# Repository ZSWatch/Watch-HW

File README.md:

# ZSWatch-Watch

## 📑 Table of Contents

- [ZSWatch-Watch](#zswatch-watch)
  - [📑 Table of Contents](#-table-of-contents)
  - [📖 About](#-about)
  - [📂 Directory Breakdown](#-directory-breakdown)
  - [Purchasing](#purchasing)
  - [KiCad library](#kicad-library)
  - [Ressources](#ressources)
  - [👨‍💻 Maintainer](#-maintainer)

## 📖 About

The **ZSWatch-Watch** project provides the hardware design and production files for a smartwatch development board tailored to the ZSWatch ecosystem.
It is built with **KiCad** and integrates a full **CI/CD pipeline** using **KiBot**, ensuring reproducible outputs for documentation, manufacturing, and releases.

Key features:

- 🛠️ Open-source hardware design
- 📦 Automated generation of Gerber, BoM, and documentation via KiBot
- 🔄 Workflow stages (DRAFT → PRELIMINARY → CHECKED → RELEASED) for structured releases
- 📝 Clear documentation and changelog to track progress
- 🌍 Designed with collaboration and transparency in mind

Please check the [wiki](https://github.com/ZSWatch/ZSWatch/wiki) for more information about the project.

You can also view this project on [CADLAB.io](...).

## 📂 Directory Breakdown

- **`.github`**: GitHub related files
- **`.gitignore`**: Ignored files list
- **`docs`**: Drawings and documentation
- **`kicad-library`**: Pinned KiCad library (submodule)
- **`scripts`**: Additional scripts for CI/CD
- **`watch`**: KiCad project for the watch
- **`CHANGELOG.md`**: Version history
- **`LICENSE`**: Project license (GPL-3.0)
- **`README.md`**: Project overview

The manufacturing outputs (Gerbers, BoM, documentation, etc.) are not part of the repository. They are
attached to each [release](https://github.com/ZSWatch/Watch-HW/releases) and published on GitHub Pages.

## Purchasing

TBD

## KiCad library

Initialize the pinned library after cloning:

```sh
git submodule update --init -- kicad-library
```

## Ressources

- [KiBot Template](https://github.com/nguyen-v/KDT_Hierarchical_KiBot)

## 👨‍💻 Maintainer

- [Daniel Kampert](mailto:danielkameprt@kampis-elektroecke.de)

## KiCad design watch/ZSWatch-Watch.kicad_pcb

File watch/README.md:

<h1 align="center">ZSWatch-Watch</h1>

<p align="center" width="100%">
  
</p>

***

<p align="center">
  
&nbsp; &nbsp; &nbsp; &nbsp;
  
</p>

***

## SPECIFICATIONS

| Parameter | Value |
| --- | --- |
| Dimensions | 32.0 × 24.0 mm |

***

## PROJECT DIRECTORY STRUCTURE

    .
    ├─ kibot_resources       # External resources for KiBot
    │  ├─ colors             # Color theme for KiCad
    │  ├─ fonts              # Fonts used in the project
    │  ├─ scripts            # External scripts used with KiBot
    │  └─ templates          # Templates for KiBot generated reports
    ├─ kibot_yaml            # KiBot YAML config files
    ├─ Logos                 # Logos
    ├─ meta                  # Project metadata
    ├─ templates             # Title block templates
    ├─ *.kicad_sch           # KiCad schematic files
    ├─ *.kicad_pcb           # KiCad PCB layout
    ├─ *.kicad_pro           # KiCad project file
    ├─ *.xml                 # Netlist of the schematic (updated by the pipeline)
    ├─ CHANGELOG.md          # Changelog of the hardware
    ├─ LICENSE               # Project license
    ├─ README.md             # Project README
    └─ kibot_launch.sh       # KiBot automation script

## OUTPUT DIRECTORY STRUCTURE

    .
    ├─ 3D                   # 3D export of the PCB (STEP)
    ├─ HTML                 # HTML files for generated webpage
    ├─ Images               # Pictures and renders
    │  └─ Logos             # Logos
    ├─ KiRI                 # KiRI (PCB diff viewer) files
    ├─ Manufacturing        # Assembly and fabrication documents
    │  ├─ Assembly          # Assembly documents (BoM, BoM check, Mouser cart, pos, notes)
    │  └─ Fabrication       # Fabrication documents (Gerber / ODB++ ZIP, notes, impedance table)
    │     ├─ Drill Tables   # CSV drill tables
    │     └─ Gerbers        # Gerbers
    ├─ Netlist              # PCB netlist
    ├─ Reports              # Reports for ERC/DRC
    ├─ Schematic            # PDF of schematic
    ├─ Testing              # Test documents
    │  └─ Testpoints        # Testpoints tables
    ├─ Variants             # Outputs for assembly variants, if available
    ├─ index.html           # Start page of the generated webpage
    └─ README.md            # This README

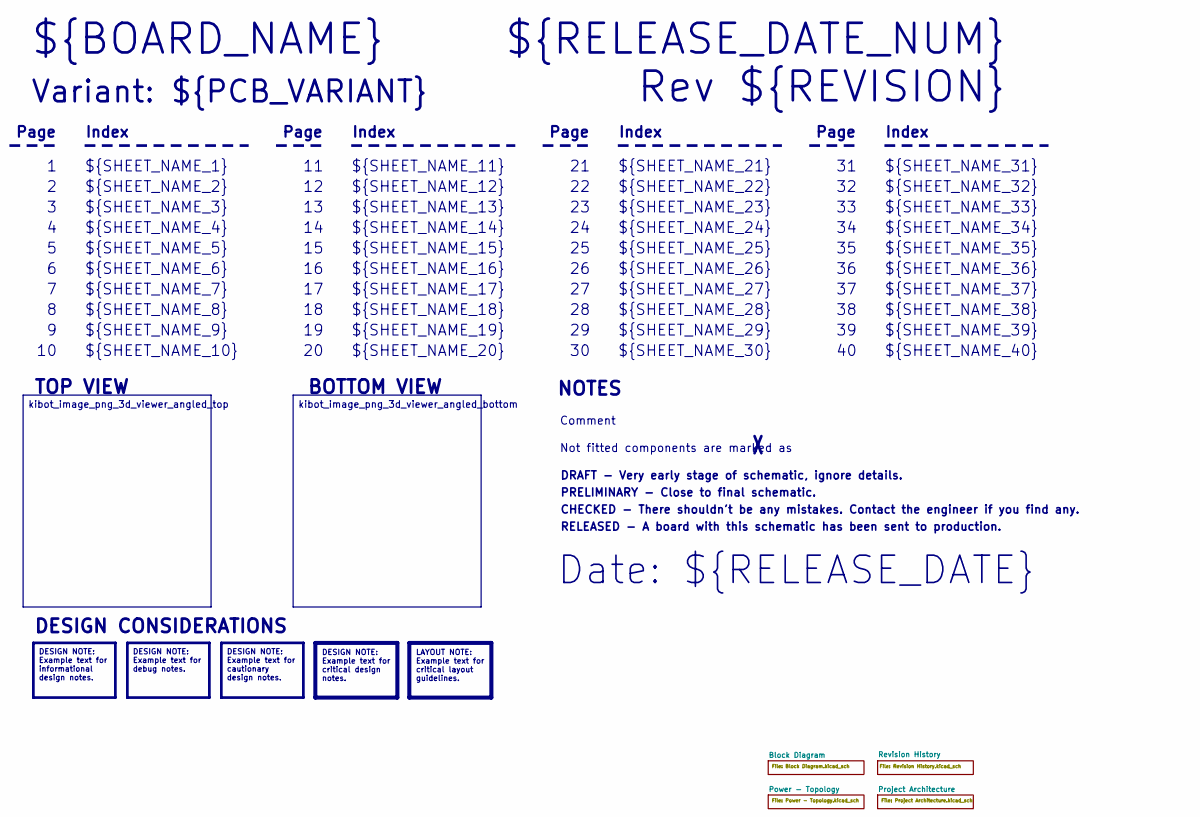
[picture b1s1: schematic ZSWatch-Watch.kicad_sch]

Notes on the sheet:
Variant: ${PCB_VARIANT}
RELEASED - A board with this schematic has been sent to production.
${SHEET_NAME_24}
Index
Page
PRELIMINARY - Close to final schematic.
${SHEET_NAME_22}
DRAFT - Very early stage of schematic, ignore details.
${SHEET_NAME_12}
${SHEET_NAME_8}
${SHEET_NAME_2}
${SHEET_NAME_5}
${SHEET_NAME_20}
${SHEET_NAME_23}
${RELEASE_DATE_NUM}
${SHEET_NAME_35}
Not fitted components are marked as
${SHEET_NAME_11}
${SHEET_NAME_6}
${SHEET_NAME_37}
${SHEET_NAME_26}
${SHEET_NAME_36}
Rev ${REVISION}
${SHEET_NAME_15}
CHECKED - There shouldn't be any mistakes. Contact the engineer if you find any.
BOTTOM VIEW
${SHEET_NAME_14}
${SHEET_NAME_21}
${SHEET_NAME_17}
${SHEET_NAME_18}
Date: ${RELEASE_DATE}
${SHEET_NAME_7}
${SHEET_NAME_31}
${BOARD_NAME}
NOTES
${SHEET_NAME_40}
${SHEET_NAME_39}
${SHEET_NAME_32}
${SHEET_NAME_1}
${SHEET_NAME_9}

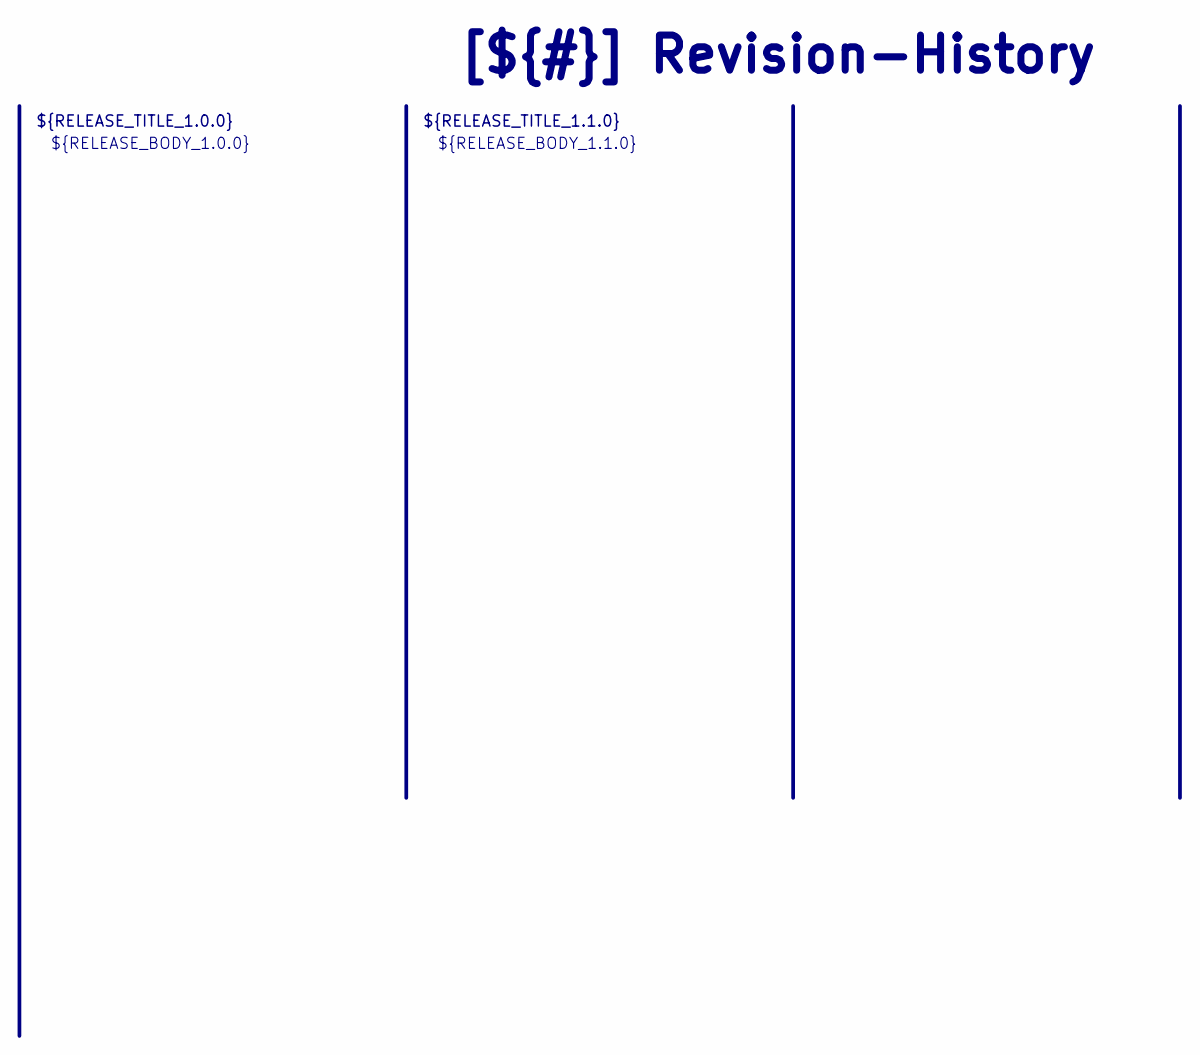
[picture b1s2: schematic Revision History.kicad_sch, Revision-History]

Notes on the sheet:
[${#}] ${TITLE}
${RELEASE_BODY_1.0.0}
${RELEASE_BODY_1.1.0}
${RELEASE_TITLE_1.0.0}
${RELEASE_TITLE_1.1.0}

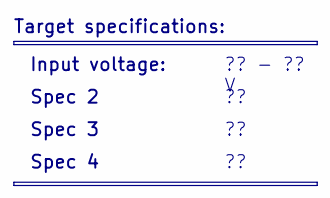
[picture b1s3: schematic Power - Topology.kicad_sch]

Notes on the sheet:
Spec 2
Input voltage:
Spec 4
?? - ?? V
Target specifications:
Spec 3

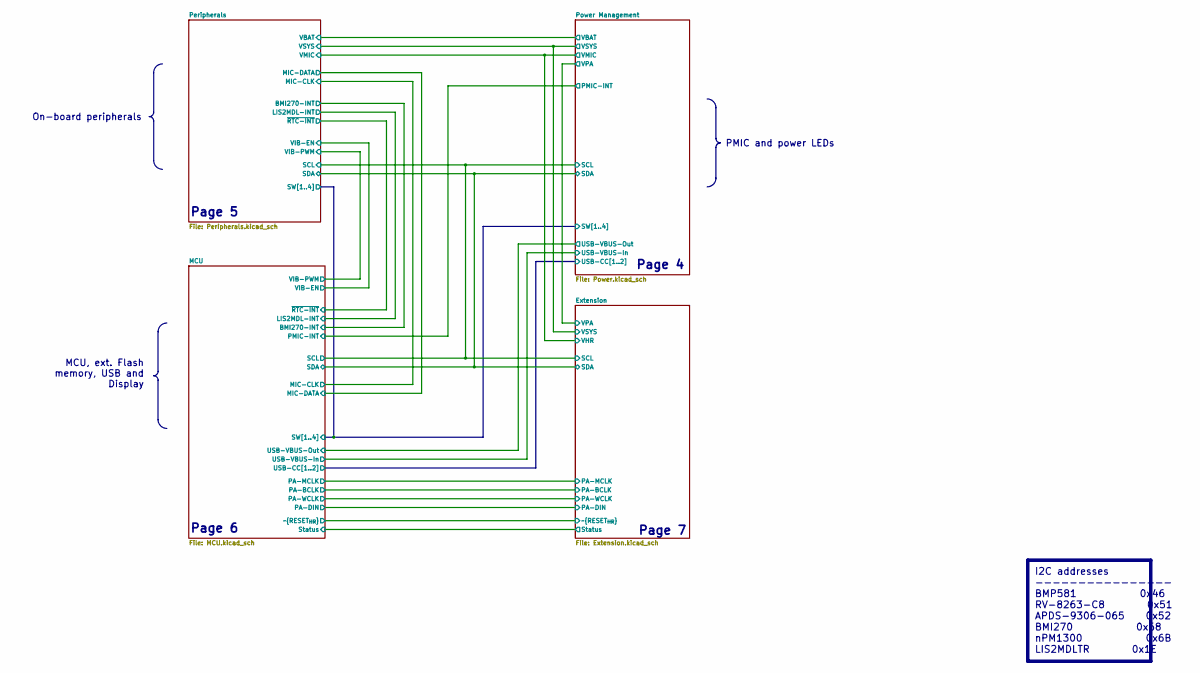
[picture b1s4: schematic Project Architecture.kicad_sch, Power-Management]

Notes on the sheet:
Page 6
Page 4
Page 7
Page 5
MCU, ext. Flash memory, USB and Display
I2C addresses ---------------- BMP581 0x46 RV-8263-C8 0x51 APDS-9306-065 0x52 BMI270 0x68 nPM1300 0x6B LIS2MDLTR 0x1E
On-board peripherals
PMIC and power LEDs

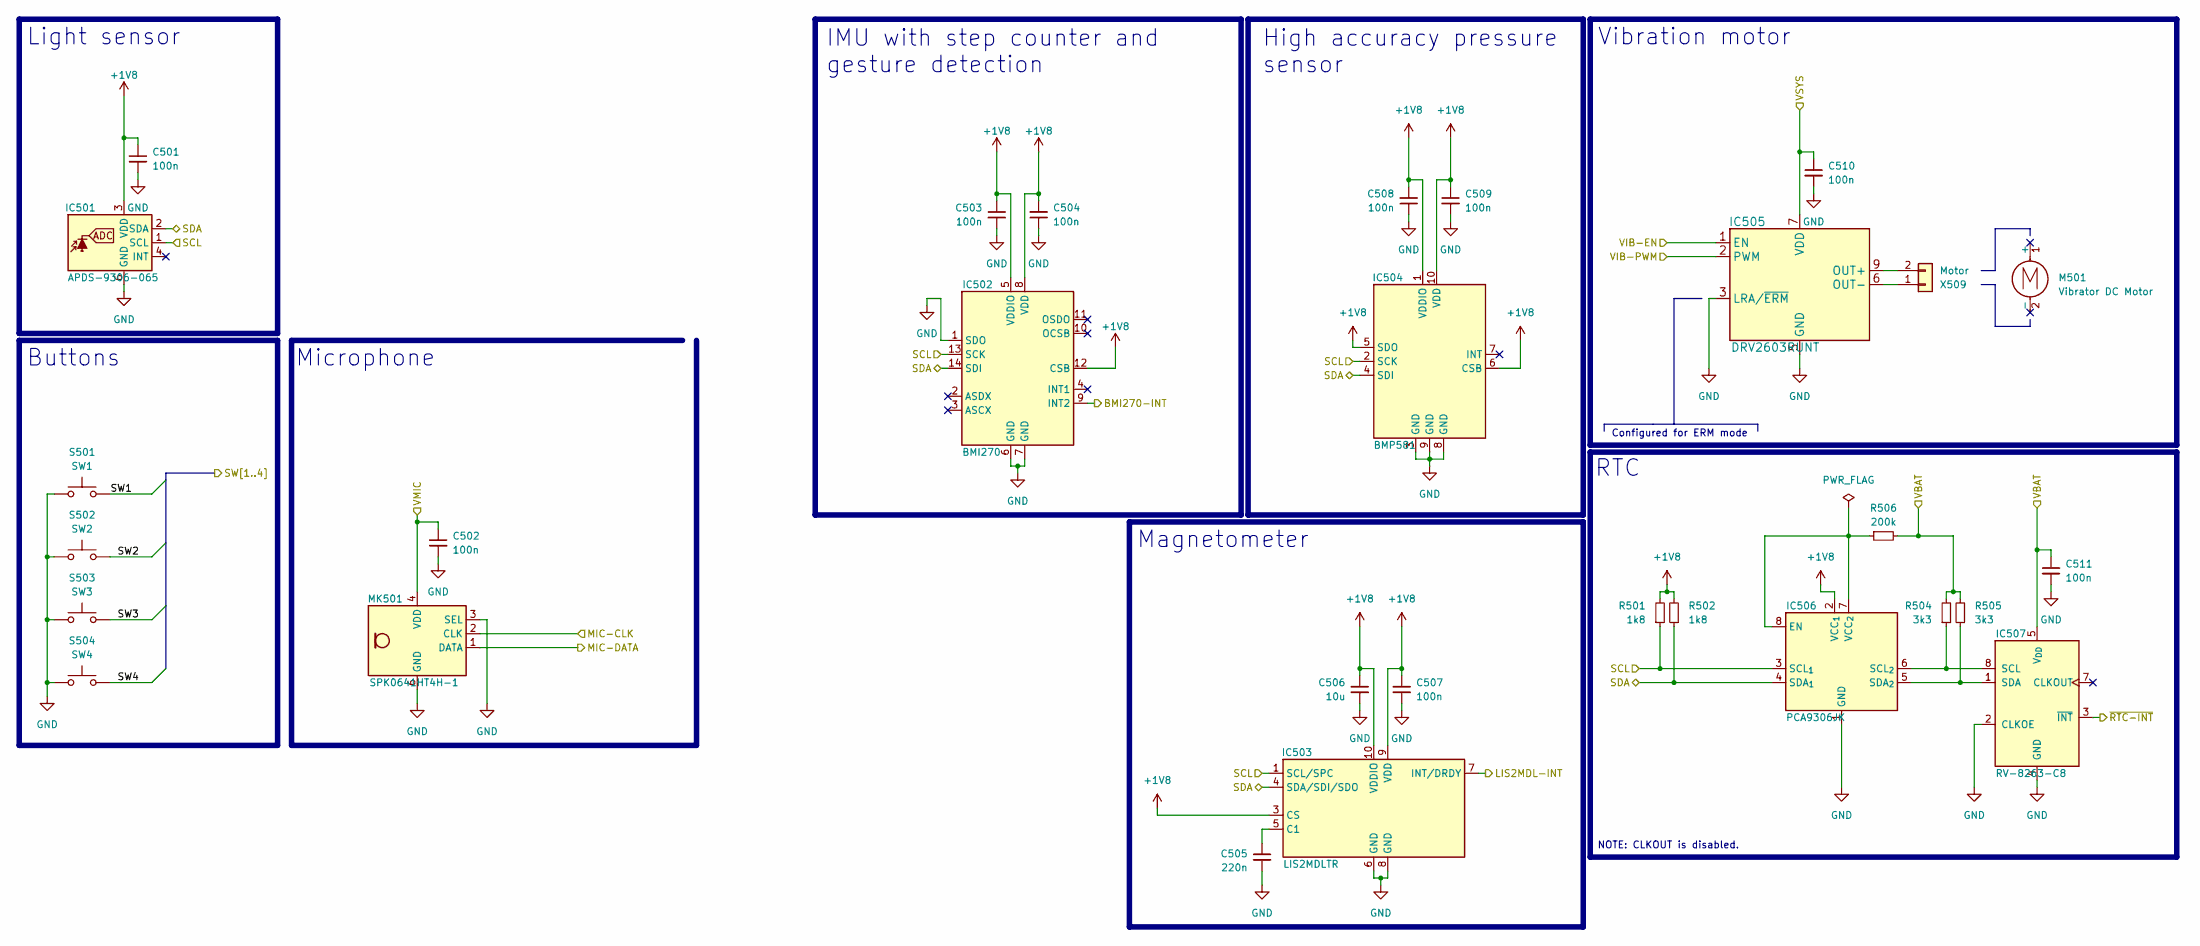
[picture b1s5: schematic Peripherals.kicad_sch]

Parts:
C501, C502, C503, C504, C507, C508, C509, C510, C511: 100n; C_0201_0603Metric; mouser# 581-02016D104MAT4A
C505: 220n; C_0201_0603Metric; mouser# 581-0201ZD224KAT2A
C506: 10u; C_0402_1005Metric; mouser# 81-GRJ155R60J106ME11D
IC501: APDS-9306-065; Broadcom_DFN-6_2x2mm_P0.65mm; mouser# 630-APDS-9306-065
IC502: BMI270; Bosch_LGA-14_3x2.5mm_P0.5mm_LayoutBorder3x4y; mouser# 262-BMI270
IC503: LIS2MDLTR; LGA-12_2x2mm_P0.5mm; mouser# 511-LIS2MDLTR
IC504: BMP581; Bosch_LGA-10_2x2mm_P0.5mm_ClockwisePinNumbering; mouser# 262-BMP581
IC505: DRV2603RUNT; WQFN-10_2x2mm_P0.5mm; mouser# 595-DRV2603RUNT
IC506: PCA9306JK; XSON-8_0.65x0.17mm_P0.35mm; mouser# 771-PCA9306JKZ
IC507: RV-8263-C8; mouser# 428-204291-MC01
M501: Vibrator DC Motor; digikey# 1670-VC1027B902F-ND
MK501: SPK0641HT4H-1; mouser# 721-SPK0641HT4H-1
R501, R502: 1k8; R_0201_0603Metric; mouser# 603-RC0201JR-071K8L
R504, R505: 3k3; R_0201_0603Metric; mouser# 603-RC0201JR-073K3L
R506: 200k; R_0201_0603Metric; mouser# 603-RC0201JR-07200KL
S501: SW1; 43633303381_NoMountingPads; mouser# 710-436333033816
S502: SW2; 43633303381_NoMountingPads; mouser# 710-436333033816
S503: SW3; 43633303381_NoMountingPads; mouser# 710-436333033816
S504: SW4; 43633303381_NoMountingPads; mouser# 710-436333033816
X509: Motor; 78171-0002; mouser# 538-78171-0002

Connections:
+1V8: C501.1, C503.1, C504.2, C506.1, C507.1, C508.2, C509.1, IC501.3 (VDD), IC502.5 (VDDIO), IC502.8 (VDD), IC502.12 (CSB), IC503.3 (CS), IC503.9 (VDD), IC503.10 (VDDIO), IC504.1 (VDDIO), IC504.5 (SDO), IC504.6 (CSB), IC504.10 (VDD), IC506.2 (VCC_{1}), R501.2, R502.2; also elsewhere on the board
/Project Architecture/Extension/SCL: IC501.1 (SCL), IC502.13 (SCK), IC503.1 (SCL/SPC), IC504.2 (SCK), IC506.3 (SCL_{1}), R501.1; also elsewhere on the board
/Project Architecture/Extension/SDA: IC501.2 (SDA), IC502.14 (SDI), IC503.4 (SDA/SDI/SDO), IC504.4 (SDI), IC506.4 (SDA_{1}), R502.1; also elsewhere on the board
/Project Architecture/Extension/VHR: C502.1, MK501.4 (VDD); also elsewhere on the board
/Project Architecture/MCU/BMI270-INT: IC502.9 (INT2); also elsewhere on the board
/Project Architecture/MCU/LIS2MDL-INT: IC503.7 (INT/DRDY); also elsewhere on the board
/Project Architecture/MCU/MIC-CLK: MK501.2 (CLK); also elsewhere on the board
/Project Architecture/MCU/MIC-DATA: MK501.1 (DATA); also elsewhere on the board
/Project Architecture/MCU/SW1: S501.2; also elsewhere on the board
/Project Architecture/MCU/SW2: S502.2; also elsewhere on the board
/Project Architecture/MCU/SW3: S503.2; also elsewhere on the board
/Project Architecture/MCU/SW4: S504.2; also elsewhere on the board
/Project Architecture/MCU/VIB-EN: IC505.1 (EN); also elsewhere on the board
/Project Architecture/MCU/VIB-PWM: IC505.2 (PWM); also elsewhere on the board
/Project Architecture/MCU/~RTC-INT: IC507.3 (~INT); also elsewhere on the board
/Project Architecture/Peripherals/VBAT: C511.1, IC507.5 (V_{DD}), R504.2, R505.2, R506.2; also elsewhere on the board
/Project Architecture/Power Management/VSYS: C510.1, IC505.7 (VDD); also elsewhere on the board
GND: C501.2, C502.2, C503.2, C504.1, C505.2, C506.2, C507.2, C508.1, C509.2, C510.2, C511.2, IC501.6 (GND), IC502.1 (SDO), IC502.6 (GND), IC502.7 (GND), IC503.6 (GND), IC503.8 (GND), IC504.3 (GND), IC504.8 (GND), IC504.9 (GND), IC505.3 (LRA/~ERM), IC505.5 (GND), IC505.8 (GND), IC505.10 (GND), IC506.1 (GND), IC507.2 (CLKOE), IC507.4 (GND), MK501.3 (SEL), MK501.5 (GND), MK501.6 (GND), MK501.7 (GND), MK501.8 (GND), S501.1, S502.1, S503.1, S504.1; also elsewhere on the board
unnamed: C505.1, IC503.5 (C1)
unnamed: IC505.9 (OUT+), X509.2
unnamed: IC505.6 (OUT-), X509.1
unnamed: IC506.7 (VCC_{2}), IC506.8 (EN), R506.1
unnamed: IC506.6 (SCL_{2}), IC507.8 (SCL), R504.1
unnamed: IC506.5 (SDA_{2}), IC507.1 (SDA), R505.1

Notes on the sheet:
Vibration motor
Magnetometer
Configured for ERM mode
High accuracy pressure sensor
Buttons
RTC
Microphone
Light sensor
IMU with step counter and gesture detection
NOTE: CLKOUT is disabled.

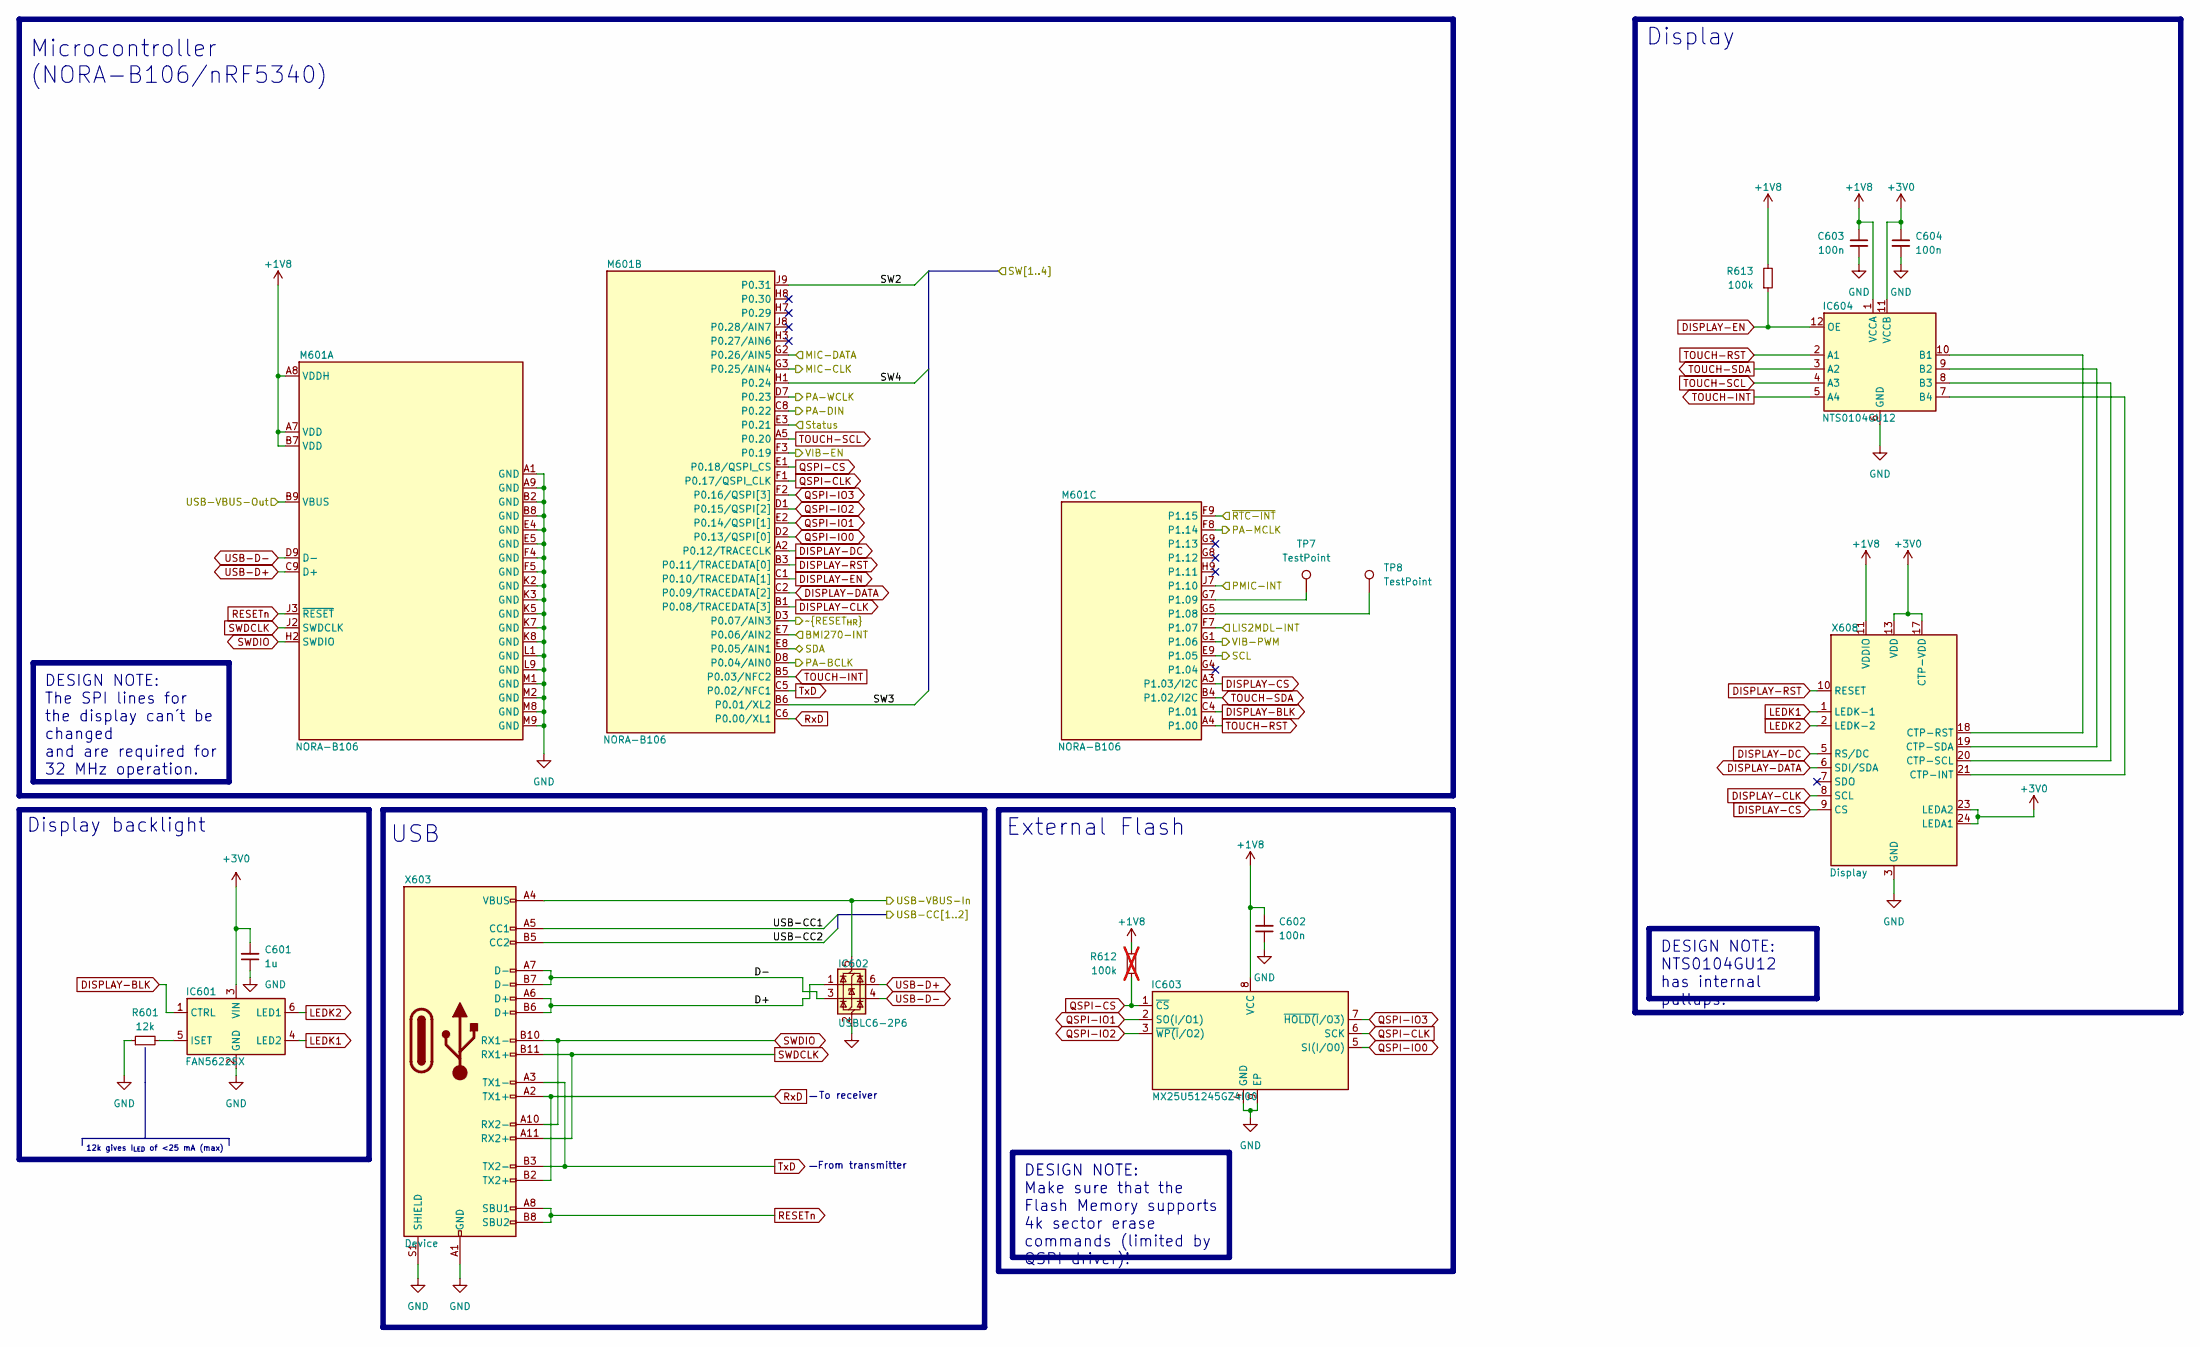
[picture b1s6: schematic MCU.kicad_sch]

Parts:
C601: 1u; C_0201_0603Metric; mouser# 581-KGM03BR50J105KH
C602, C603, C604: 100n; C_0201_0603Metric; mouser# 581-02016D104MAT4A
IC601: FAN5622SX; TSOT-23-6; mouser# 512-FAN5622SX
IC602: USBLC6-2P6; SOT-666; mouser# 511-USBLC6-2P6
IC603: MX25U51245GZ4I00; WSON-8-1EP_8x6mm_P1.27mm_EP3.4x4.3mm; mouser# 95-25U51245GZ4I00T
IC604: NTS0104GU12; XQFN-12-1.7x2mm_P0.4mm; mouser# 771-NTS0104GU12115
M601: NORA-B106; mouser# 377-NORA-B106-00B
R601: 12k; R_0201_0603Metric; mouser# 603-RC0201JR-0712KL
R612: 100k; R_0201_0603Metric; mouser# 603-RC0201JR-07100KL; not fitted
R613: 100k; R_0201_0603Metric; mouser# 603-RC0201JR-07100KL
TP7, TP8: TestPoint; TestPoint_Pad_D1.0mm
X603: Device; USB_C_Receptacle_Amphenol_12401610E4-2A; mouser# 523-12401610E4#2A
X608: Display; ER-CON0.4-24P

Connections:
+1V8: C602.2, C603.1, IC603.8 (VCC), IC604.1 (VCCA), M601.A7 (VDD), M601.A8 (VDDH), M601.B7 (VDD), R612.1, R613.2, X608.11 (VDDIO), X608.12 (VDDIO); also elsewhere on the board
+3V0: C601.2, C604.1, IC601.3 (VIN), IC604.11 (VCCB), X608.13 (VDD), X608.14 (VDD), X608.17 (CTP-VDD), X608.23 (LEDA2), X608.24 (LEDA1); also elsewhere on the board
/Project Architecture/Extension/PA-BCLK: M601.D8 (P0.04/AIN0); also elsewhere on the board
/Project Architecture/Extension/PA-DIN: M601.C8 (P0.22); also elsewhere on the board
/Project Architecture/Extension/PA-MCLK: M601.F8 (P1.14); also elsewhere on the board
/Project Architecture/Extension/PA-WCLK: M601.D7 (P0.23); also elsewhere on the board
/Project Architecture/Extension/SCL: M601.E9 (P1.05); also elsewhere on the board
/Project Architecture/Extension/SDA: M601.E8 (P0.05/AIN1); also elsewhere on the board
/Project Architecture/Extension/Status: M601.E3 (P0.21); also elsewhere on the board
/Project Architecture/Extension/~RESET_{HR}: M601.D3 (P0.07/AIN3); also elsewhere on the board
/Project Architecture/MCU/BMI270-INT: M601.E7 (P0.06/AIN2); also elsewhere on the board
/Project Architecture/MCU/D+: IC602.1 (I/O1), X603.A6 (D+), X603.B6 (D+)
/Project Architecture/MCU/D-: IC602.3 (I/O2), X603.A7 (D-), X603.B7 (D-)
/Project Architecture/MCU/LIS2MDL-INT: M601.F7 (P1.07); also elsewhere on the board
/Project Architecture/MCU/MIC-CLK: M601.G3 (P0.25/AIN4); also elsewhere on the board
/Project Architecture/MCU/MIC-DATA: M601.G2 (P0.26/AIN5); also elsewhere on the board
/Project Architecture/MCU/PMIC-INT: M601.J7 (P1.10); also elsewhere on the board
/Project Architecture/MCU/SW2: M601.J9 (P0.31); also elsewhere on the board
/Project Architecture/MCU/SW3: M601.B6 (P0.01/XL2); also elsewhere on the board
/Project Architecture/MCU/SW4: M601.H1 (P0.24); also elsewhere on the board
/Project Architecture/MCU/USB-CC1: X603.A5 (CC1); also elsewhere on the board
/Project Architecture/MCU/USB-CC2: X603.B5 (CC2); also elsewhere on the board
/Project Architecture/MCU/USB-VBUS-In: IC602.5 (VBUS), X603.A4 (VBUS), X603.A9 (VBUS), X603.B4 (VBUS), X603.B9 (VBUS); also elsewhere on the board
/Project Architecture/MCU/USB-VBUS-Out: M601.B9 (VBUS); also elsewhere on the board
/Project Architecture/MCU/VIB-EN: M601.F3 (P0.19); also elsewhere on the board
/Project Architecture/MCU/VIB-PWM: M601.G1 (P1.06); also elsewhere on the board
/Project Architecture/MCU/~RTC-INT: M601.F9 (P1.15); also elsewhere on the board
DISPLAY-BLK: IC601.1 (CTRL), M601.C4 (P1.01)
DISPLAY-CLK: M601.B1 (P0.08/TRACEDATA[3]), X608.8 (SCL)
DISPLAY-CS: M601.A3 (P1.03/I2C), X608.9 (CS)
DISPLAY-DATA: M601.C2 (P0.09/TRACEDATA[2]), X608.6 (SDI/SDA)
DISPLAY-DC: M601.A2 (P0.12/TRACECLK), X608.5 (RS/DC)
DISPLAY-EN: IC604.12 (OE), M601.C1 (P0.10/TRACEDATA[1]), R613.1
DISPLAY-RST: M601.B3 (P0.11/TRACEDATA[0]), X608.10 (RESET)
GND: C601.1, C602.1, C603.2, C604.2, IC601.2 (GND), IC602.2 (GND), IC603.4 (GND), IC603.9 (EP), IC604.6 (GND), M601.A1 (GND), M601.A9 (GND), M601.B2 (GND), M601.B8 (GND), M601.E4 (GND), M601.E5 (GND), M601.F4 (GND), M601.F5 (GND), M601.K2 (GND), M601.K3 (GND), M601.K5 (GND), M601.K7 (GND), M601.K8 (GND), M601.L1 (GND), M601.L9 (GND), M601.M1 (GND), M601.M2 (GND), M601.M8 (GND), M601.M9 (GND), R601.1, X603.A1 (GND), X603.A12 (GND), X603.B1 (GND), X603.B12 (GND), X603.S1 (SHIELD), X608.3 (GND), X608.4 (GND), X608.15 (GND), X608.16 (GND); also elsewhere on the board
LEDK1: IC601.4 (LED2), X608.1 (LEDK-1)
LEDK2: IC601.6 (LED1), X608.2 (LEDK-2)
unnamed: IC601.5 (ISET), R601.2
unnamed: IC604.10 (B1), X608.18 (CTP-RST)
unnamed: IC604.9 (B2), X608.19 (CTP-SDA)
unnamed: IC604.8 (B3), X608.20 (CTP-SCL)
unnamed: IC604.7 (B4), X608.21 (CTP-INT)
unnamed: M601.G5 (P1.08), TP8.1
unnamed: M601.G7 (P1.09), TP7.1
QSPI-CLK: IC603.6 (SCK), M601.F1 (P0.17/QSPI_CLK)
QSPI-CS: IC603.1 (~CS), M601.E1 (P0.18/QSPI_CS), R612.2
QSPI-IO0: IC603.5 (SI(I/O0)), M601.D2 (P0.13/QSPI[0])
QSPI-IO1: IC603.2 (SO(I/O1)), M601.E2 (P0.14/QSPI[1])
QSPI-IO2: IC603.3 (~WP(I/O2)), M601.D1 (P0.15/QSPI[2])
QSPI-IO3: IC603.7 (~HOLD(I/O3)), M601.F2 (P0.16/QSPI[3])
RESETn: M601.J3 (~RESET), X603.A8 (SBU1), X603.B8 (SBU2)
RxD: M601.C6 (P0.00/XL1), X603.A2 (TX1+), X603.B2 (TX2+)
SWDCLK: M601.J2 (SWDCLK), X603.A11 (RX2+), X603.B11 (RX1+)
SWDIO: M601.H2 (SWDIO), X603.A10 (RX2-), X603.B10 (RX1-)
TOUCH-INT: IC604.5 (A4), M601.B5 (P0.03/NFC2)
TOUCH-RST: IC604.2 (A1), M601.A4 (P1.00)
TOUCH-SCL: IC604.4 (A3), M601.A5 (P0.20)
TOUCH-SDA: IC604.3 (A2), M601.B4 (P1.02/I2C)
TxD: M601.C5 (P0.02/NFC1), X603.A3 (TX1-), X603.B3 (TX2-)
USB-D+: IC602.6 (I/O1), M601.C9 (D+)
USB-D-: IC602.4 (I/O2), M601.D9 (D-)

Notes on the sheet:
From transmitter
To receiver
12k gives I_{LED} of <25 mA (max)
Display backlight
Display
USB
Microcontroller (NORA-B106/nRF5340)
External Flash
DESIGN NOTE: NTS0104GU12 has internal pullups.
DESIGN NOTE: Make sure that the Flash Memory supports 4k sector erase commands (limited by QSPI driver)!
DESIGN NOTE: The SPI lines for the display can´t be changed and are required for 32 MHz operation.

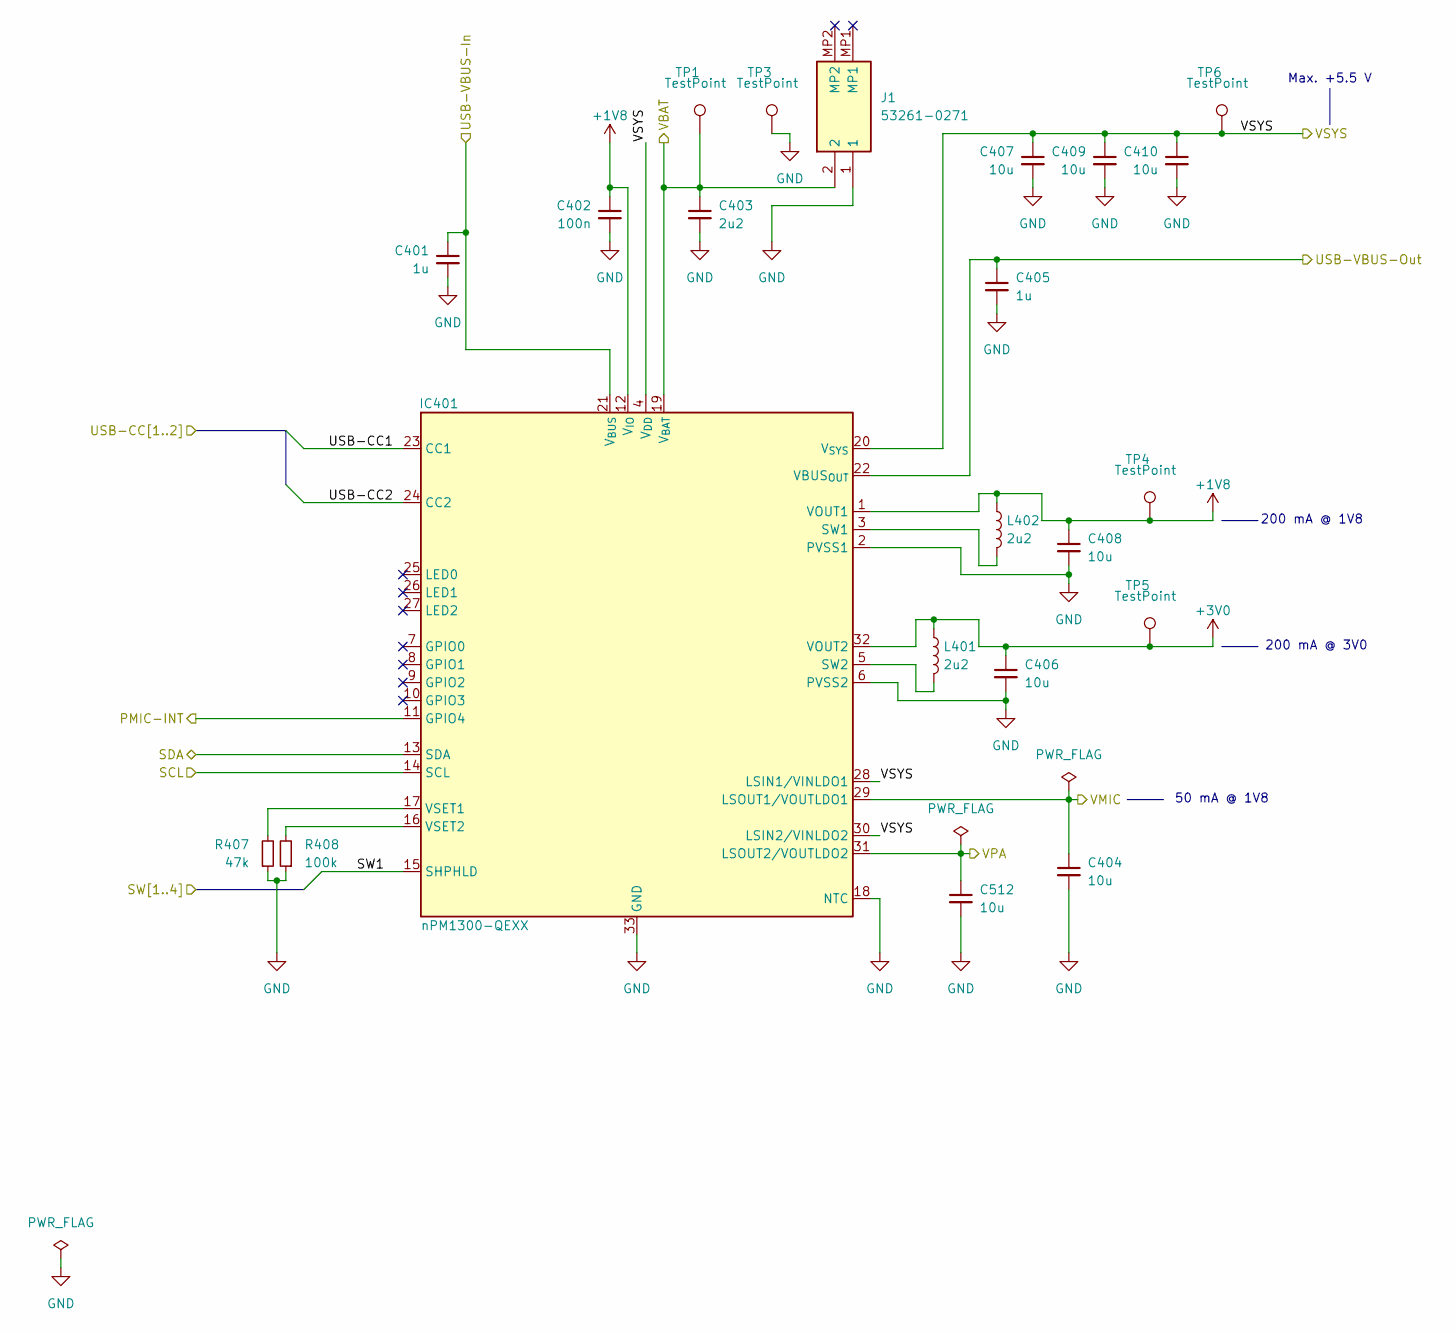
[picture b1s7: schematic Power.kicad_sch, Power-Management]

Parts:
C401, C405: 1u; C_0201_0603Metric; mouser# 581-KGM03BR50J105KH
C402: 100n; C_0201_0603Metric; mouser# 581-02016D104MAT4A
C403: 2u2; C_0402_1005Metric; mouser# 581-0402ZD225MAT2A
C404, C406, C408, C512: 10u; C_0402_1005Metric; mouser# 81-GRJ155R60J106ME11D
C407, C409, C410: 10u; C_0603_1608Metric; mouser# 581-KGM15CR50J106MT
IC401: nPM1300-QEXX; QFN-32-1EP_5x5mm_P0.5mm_EP3.6x3.6mm; mouser# 949-NPM1300-QEAA-R7
J1: 53261-0271; molex_pico; mouser# 538-53261-0271
L401, L402: 2u2; L_0603_1608Metric; mouser# 81-LQM18PZ2R2MDHD
R407: 47k; R_0201_0603Metric; mouser# 603-RC0201JR-0747KL
R408: 100k; R_0201_0603Metric; mouser# 603-RC0201JR-07100KL
TP1, TP3: TestPoint; TestPoint_Loop_D3.50mm_Drill0.9mm_Beaded
TP4, TP5, TP6: TestPoint; TestPoint_Pad_D1.0mm

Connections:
+1V8: C402.1, C408.1, IC401.1 (VOUT1), IC401.12 (V_{IO}), L402.1, TP4.1; also elsewhere on the board
+3V0: C406.1, IC401.32 (VOUT2), L401.1, TP5.1; also elsewhere on the board
/Project Architecture/Extension/SCL: IC401.14 (SCL); also elsewhere on the board
/Project Architecture/Extension/SDA: IC401.13 (SDA); also elsewhere on the board
/Project Architecture/Extension/VHR: C404.1, IC401.29 (LSOUT1/VOUTLDO1); also elsewhere on the board
/Project Architecture/Extension/VPA: C512.1, IC401.31 (LSOUT2/VOUTLDO2); also elsewhere on the board
/Project Architecture/MCU/PMIC-INT: IC401.11 (GPIO4); also elsewhere on the board
/Project Architecture/MCU/SW1: IC401.15 (SHPHLD); also elsewhere on the board
/Project Architecture/MCU/USB-CC1: IC401.23 (CC1); also elsewhere on the board
/Project Architecture/MCU/USB-CC2: IC401.24 (CC2); also elsewhere on the board
/Project Architecture/MCU/USB-VBUS-In: C401.1, IC401.21 (V_{BUS}); also elsewhere on the board
/Project Architecture/MCU/USB-VBUS-Out: C405.1, IC401.22 (VBUS_{OUT}); also elsewhere on the board
/Project Architecture/Peripherals/VBAT: C403.1, IC401.19 (V_{BAT}), J1.2, TP1.1; also elsewhere on the board
/Project Architecture/Power Management/VSYS: C407.1, C409.1, C410.1, IC401.4 (V_{DD}), IC401.20 (V_{SYS}), IC401.28 (LSIN1/VINLDO1), IC401.30 (LSIN2/VINLDO2), TP6.1; also elsewhere on the board
GND: C401.2, C402.2, C403.2, C404.2, C405.2, C406.2, C407.2, C408.2, C409.2, C410.2, C512.2, IC401.2 (PVSS1), IC401.6 (PVSS2), IC401.18 (NTC), IC401.33 (GND), J1.1, R407.1, R408.1, TP3.1; also elsewhere on the board
unnamed: IC401.3 (SW1), L402.2
unnamed: IC401.5 (SW2), L401.2
unnamed: IC401.17 (VSET1), R407.2
unnamed: IC401.16 (VSET2), R408.2

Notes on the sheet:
50 mA @ 1V8
200 mA @ 1V8
Max. +5.5 V
200 mA @ 3V0

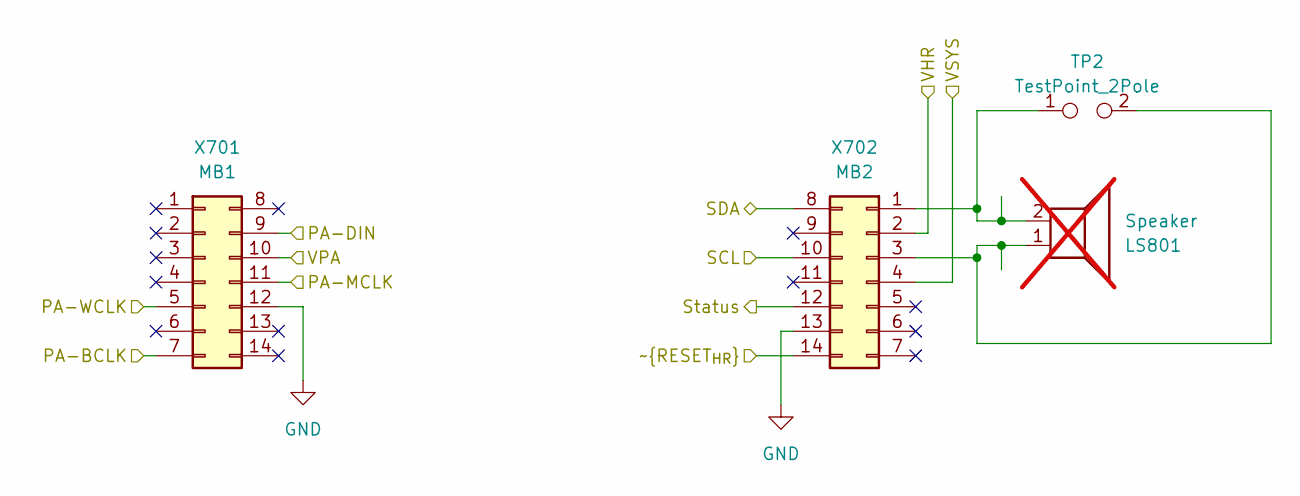
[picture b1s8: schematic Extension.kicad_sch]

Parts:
LS801: Speaker; CMR-12062S-67; mouser# 490-CMR-12062S-67; not fitted
TP2: TestPoint_2Pole; TestPoint_2Pads_Pitch2.54mm_Drill0.8mm
X701: MB1; 101R014FB110; mouser# 649-101R014FB110
X702: MB2; 101R014FB110; mouser# 649-101R014FB110

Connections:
/Project Architecture/Extension/PA-BCLK: X701.7; also elsewhere on the board
/Project Architecture/Extension/PA-DIN: X701.9; also elsewhere on the board
/Project Architecture/Extension/PA-MCLK: X701.11; also elsewhere on the board
/Project Architecture/Extension/PA-WCLK: X701.5; also elsewhere on the board
/Project Architecture/Extension/SCL: X702.10; also elsewhere on the board
/Project Architecture/Extension/SDA: X702.8; also elsewhere on the board
/Project Architecture/Extension/Status: X702.12; also elsewhere on the board
/Project Architecture/Extension/VHR: X702.2; also elsewhere on the board
/Project Architecture/Extension/VPA: X701.10; also elsewhere on the board
/Project Architecture/Extension/~RESET_{HR}: X702.14; also elsewhere on the board
/Project Architecture/Power Management/VSYS: X702.4; also elsewhere on the board
GND: X701.12, X702.13; also elsewhere on the board
unnamed: LS801.2, TP2.1, X702.1
unnamed: LS801.1, TP2.2, X702.3

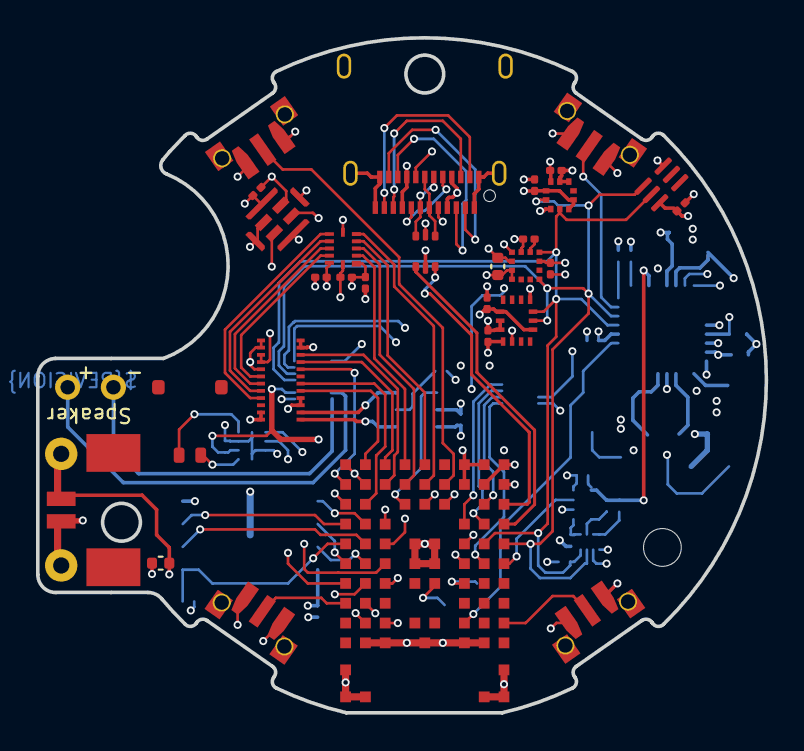
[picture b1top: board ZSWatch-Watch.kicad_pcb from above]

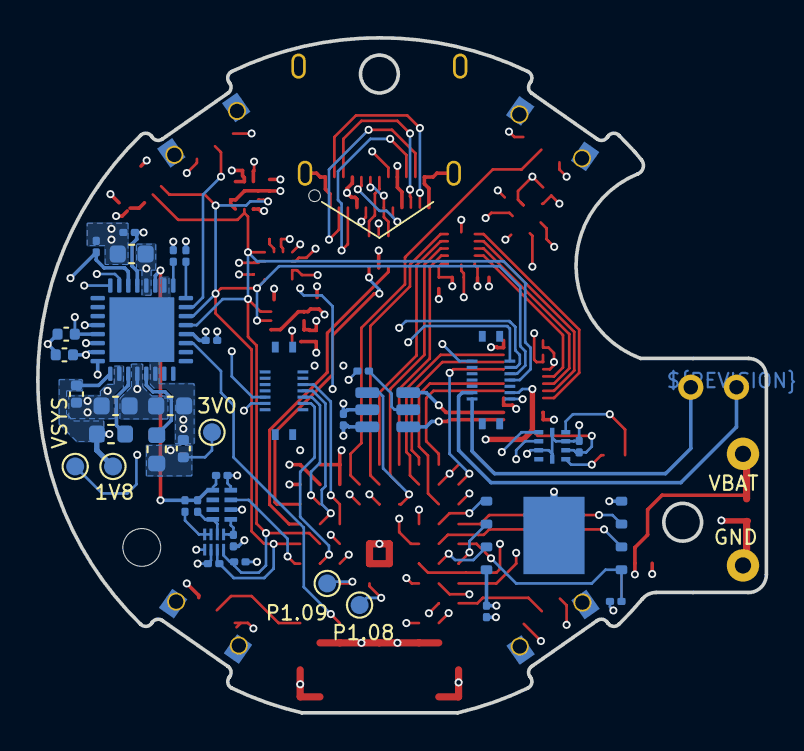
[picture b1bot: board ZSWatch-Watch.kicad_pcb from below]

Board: 4 copper layers, 40.5 x 37.5 mm, 70 parts (38 on the bottom side), 78 nets.
